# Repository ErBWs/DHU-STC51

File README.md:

# DHU-STC51
该仓库包含两套东华大学 STC51 相关代码及仿真文件 

## A9

微机系统设计与实践综合设计：A9.多路温度检测仪的设计

(这个可以正常运行)

## Heater

电子系统设计与实践：温控器(加热)

(伪代码，跑不起来的)

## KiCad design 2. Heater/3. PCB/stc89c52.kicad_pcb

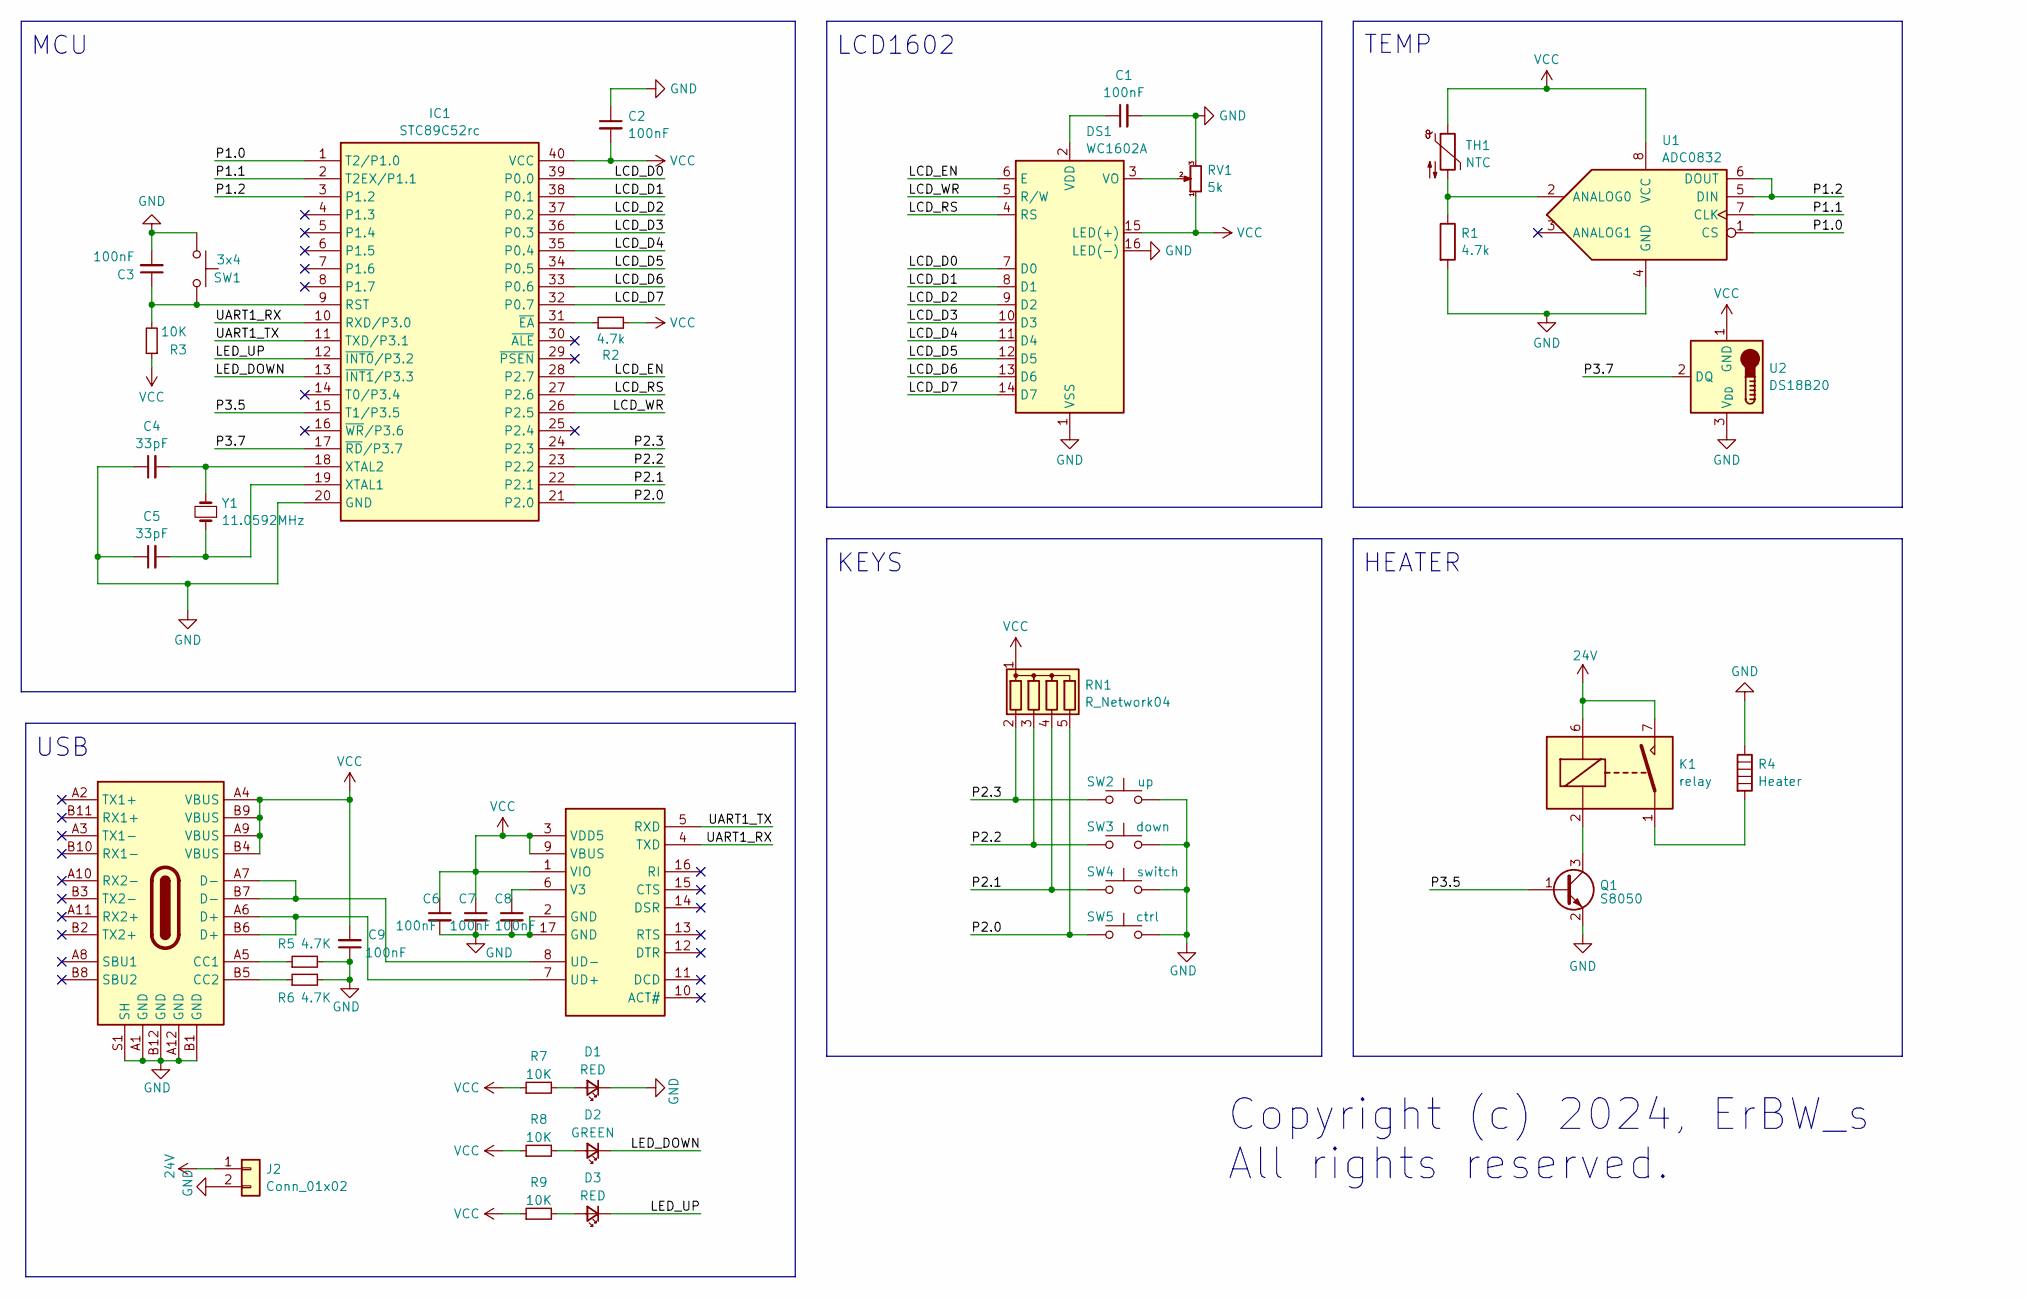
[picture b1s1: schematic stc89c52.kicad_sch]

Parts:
C1, C2, C3, C6, C7, C8, C9: 100nF; C_0603_1608Metric
C4, C5: 33pF; C_0603_1608Metric
D1, D3: RED; LED_0805_2012Metric
D2: GREEN; LED_0805_2012Metric
DS1: WC1602A
IC1: STC89C52rc; DIP-40_W15.24mm; Manufacturer_Part_Number STC89C52rc
J1: USB-Type-C; USB-Type-C_SMD_16P
J2: Conn_01x02; VCC_CONN
K1: relay; Relay_StandexMeder_DIP_LowProfile
Q1: S8050; SOT-23
R1, R2: 4.7k; R_0603_1608Metric
R3, R7, R8, R9: 10K; R_0603_1608Metric
R4: Heater; PinHeader_1x02_P2.54mm_Vertical
R5, R6: 4.7K; R_0603_1608Metric
RN1: R_Network04; R_Array_SIP5
RV1: 5k; 3296W
SW1: 3x4; BUTTON_3x4
SW2: up; BUTTON_3x4
SW3: down; BUTTON_3x4
SW4: switch; BUTTON_3x4
SW5: ctrl; BUTTON_3x4
TH1: NTC; PinHeader_1x02_P2.54mm_Vertical
U1: ADC0832; DIP-8_W7.62mm
U2: DS18B20; TO-92_Inline
U3: CH343P; QFN-16-1EP_3x3mm_P0.5mm_EP1.7x1.7mm
Y1: 11.0592MHz; Crystal_SMD_3215_FC-135_2P

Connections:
24V: J2.1, K1.6, K1.7, K1.8
/LCD_D0: DS1.7 (D0), IC1.39 (P0.0)
/LCD_D1: DS1.8 (D1), IC1.38 (P0.1)
/LCD_D2: DS1.9 (D2), IC1.37 (P0.2)
/LCD_D3: DS1.10 (D3), IC1.36 (P0.3)
/LCD_D4: DS1.11 (D4), IC1.35 (P0.4)
/LCD_D5: DS1.12 (D5), IC1.34 (P0.5)
/LCD_D6: DS1.13 (D6), IC1.33 (P0.6)
/LCD_D7: DS1.14 (D7), IC1.32 (P0.7)
/LCD_EN: DS1.6 (E), IC1.28 (P2.7)
/LCD_RS: DS1.4 (RS), IC1.27 (P2.6)
/LCD_WR: DS1.5 (R/W), IC1.26 (P2.5)
/LED_DOWN: D2.2 (A), IC1.13 (~INT1/P3.3)
/LED_UP: D3.2 (A), IC1.12 (~INT0/P3.2)
/P1.0: IC1.1 (T2/P1.0), U1.1 (CS)
/P1.1: IC1.2 (T2EX/P1.1), U1.7 (CLK)
/P1.2: IC1.3 (P1.2), U1.5 (DIN), U1.6 (DOUT)
/P2.0: IC1.21 (P2.0), RN1.5 (R4), SW5.1
/P2.1: IC1.22 (P2.1), RN1.4 (R3), SW4.1
/P2.2: IC1.23 (P2.2), RN1.3 (R2), SW3.1
/P2.3: IC1.24 (P2.3), RN1.2 (R1), SW2.1
/P3.5: IC1.15 (T1/P3.5), Q1.1 (B)
/P3.7: IC1.17 (~RD/P3.7), U2.2 (DQ)
/UART1_RX: IC1.10 (RXD/P3.0), U3.4 (TXD)
/UART1_TX: IC1.11 (TXD/P3.1), U3.5 (RXD)
GND: C1.2, C2.1, C3.2, C4.1, C5.1, C6.2, C7.2, C8.2, C9.1, D1.2 (A), DS1.1 (VSS), DS1.16 (LED(-)), IC1.20 (GND), J1.A1 (GND), J1.A12 (GND), J1.B1 (GND), J1.B12 (GND), J1.S1 (SH), J2.2, Q1.2 (E), R1.2, R4.1, R5.2, R6.2, RV1.3, SW1.1, SW2.2, SW3.2, SW4.2, SW5.2, U1.4 (GND), U2.3 (V_{DD}), U3.2 (GND), U3.17 (GND)
unnamed: D1.1 (K), R7.2
unnamed: D2.1 (K), R8.2
unnamed: D3.1 (K), R9.2
unnamed: C1.1, DS1.2 (VDD)
unnamed: DS1.3 (VO), RV1.2
unnamed: C3.1, IC1.9 (RST), R3.2, SW1.2
unnamed: C5.2, IC1.19 (XTAL1), Y1.1
unnamed: C4.2, IC1.18 (XTAL2), Y1.2
unnamed: IC1.31 (~EA), R2.1
unnamed: J1.A5 (CC1), R5.1
unnamed: J1.B5 (CC2), R6.1
unnamed: K1.1, K1.14, R4.2
unnamed: K1.2, Q1.3 (C)
unnamed: R1.1, TH1.2, U1.2 (ANALOG0)
unnamed: J1.A6 (D+), J1.B6 (D+), U3.7 (UD+)
unnamed: J1.A7 (D-), J1.B7 (D-), U3.8 (UD-)
unnamed: C8.1, U3.6 (V3)
VCC: C2.2, C6.1, C7.1, C9.2, DS1.15 (LED(+)), IC1.40 (VCC), J1.A4 (VBUS), J1.A9 (VBUS), J1.B4 (VBUS), J1.B9 (VBUS), R2.2, R3.1, R7.1, R8.1, R9.1, RN1.1 (common), RV1.1, TH1.1, U1.8 (VCC), U2.1 (GND), U3.1 (VIO), U3.3 (VDD5), U3.9 (VBUS)

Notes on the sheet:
TEMP
MCU
USB
Copyright (c) 2024, ErBW_s All rights reserved.
LCD1602
KEYS
HEATER

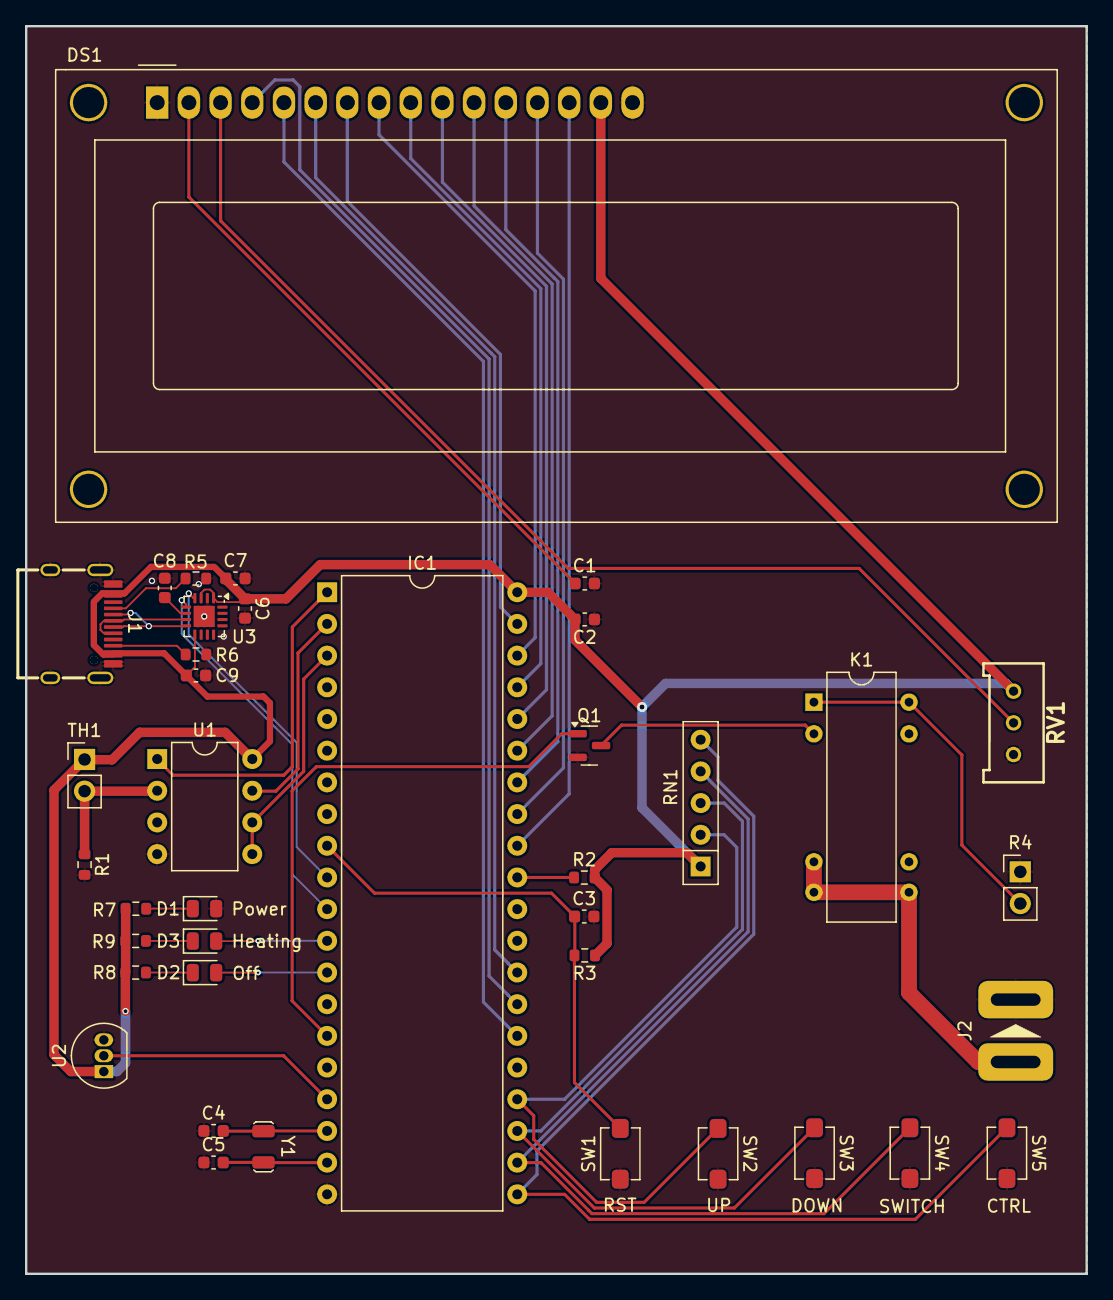
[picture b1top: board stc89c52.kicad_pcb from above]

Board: 2 copper layers, 85.0 x 100.0 mm, 39 parts (0 on the bottom side), 44 nets.

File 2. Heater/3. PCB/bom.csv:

"Reference","Value","Datasheet","Footprint","Qty","DNP"
"C1,C2,C3,C6,C7,C8,C9","100nF","~","Capacitor_SMD:C_0603_1608Metric","7",""
"C4,C5","33pF","~","Capacitor_SMD:C_0603_1608Metric","2",""
"D1,D3","RED","~","LED_SMD:LED_0805_2012Metric","2",""
"D2","GREEN","~","LED_SMD:LED_0805_2012Metric","1",""
"DS1","WC1602A","http://www.wincomlcd.com/pdf/WC1602A-SFYLYHTC06.pdf","Display:WC1602A","1",""
"IC1","STC89C52rc","http://www.stcmicro.com/datasheet/STC89C51RC-en.pdf","Package_DIP:DIP-40_W15.24mm","1",""
"J1","USB-Type-C","","ErBW_s:USB-Type-C_SMD_16P","1",""
"K1","relay","https://standexelectronics.com/wp-content/uploads/datasheet_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","Relay_THT:Relay_StandexMeder_DIP_LowProfile","1",""
"Q1","S8050","http://www.onsemi.com/pub_link/Collateral/2N3055-D.PDF","Package_TO_SOT_SMD:SOT-23","1",""
"R1,R2","4.7k","~","Resistor_SMD:R_0603_1608Metric","2",""
"R3,R7,R8,R9","10K","~","Resistor_SMD:R_0603_1608Metric","4",""
"R4","Heater","~","Connector_PinHeader_2.54mm:PinHeader_1x02_P2.54mm_Vertical","1",""
"R5,R6","4.7K","~","Resistor_SMD:R_0603_1608Metric","2",""
"RN1","R_Network04","http://www.vishay.com/docs/31509/csc.pdf","Resistor_THT:R_Array_SIP5","1",""
"RV1","5k","~","ErBW_s:3296W","1",""
"SW1","3x4","~","ErBW_s:BUTTON_3x4","1",""
"SW2","up","~","ErBW_s:BUTTON_3x4","1",""
"SW3","down","~","ErBW_s:BUTTON_3x4","1",""
"SW4","switch","~","ErBW_s:BUTTON_3x4","1",""
"SW5","ctrl","~","ErBW_s:BUTTON_3x4","1",""
"TH1","NTC","~","Connector_PinHeader_2.54mm:PinHeader_1x02_P2.54mm_Vertical","1",""
"U1","ADC0832","http://www.ti.com/lit/ds/symlink/adc0831-n.pdf","Package_DIP:DIP-8_W7.62mm","1",""
"U2","DS18B20","http://datasheets.maximintegrated.com/en/ds/DS18B20.pdf","Package_TO_SOT_THT:TO-92_Inline","1",""
"U3","CH343P","","Package_DFN_QFN:QFN-16-1EP_3x3mm_P0.5mm_EP1.7x1.7mm","1",""
"Y1","11.0592MHz","~","ErBW_s:Crystal_SMD_3215_FC-135_2P","1",""

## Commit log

2024-01-03 add uart
2024-01-03 完成使用数码管显示方案
2024-01-06 完成使用LCD1602显示方案
2024-01-14 final fix
2025-02-17 fix: better header includes
2025-02-17 add heater
2025-02-17 update hex file path
2025-02-17 update code
2025-02-18 add bom
2025-02-19 add 24v conn
